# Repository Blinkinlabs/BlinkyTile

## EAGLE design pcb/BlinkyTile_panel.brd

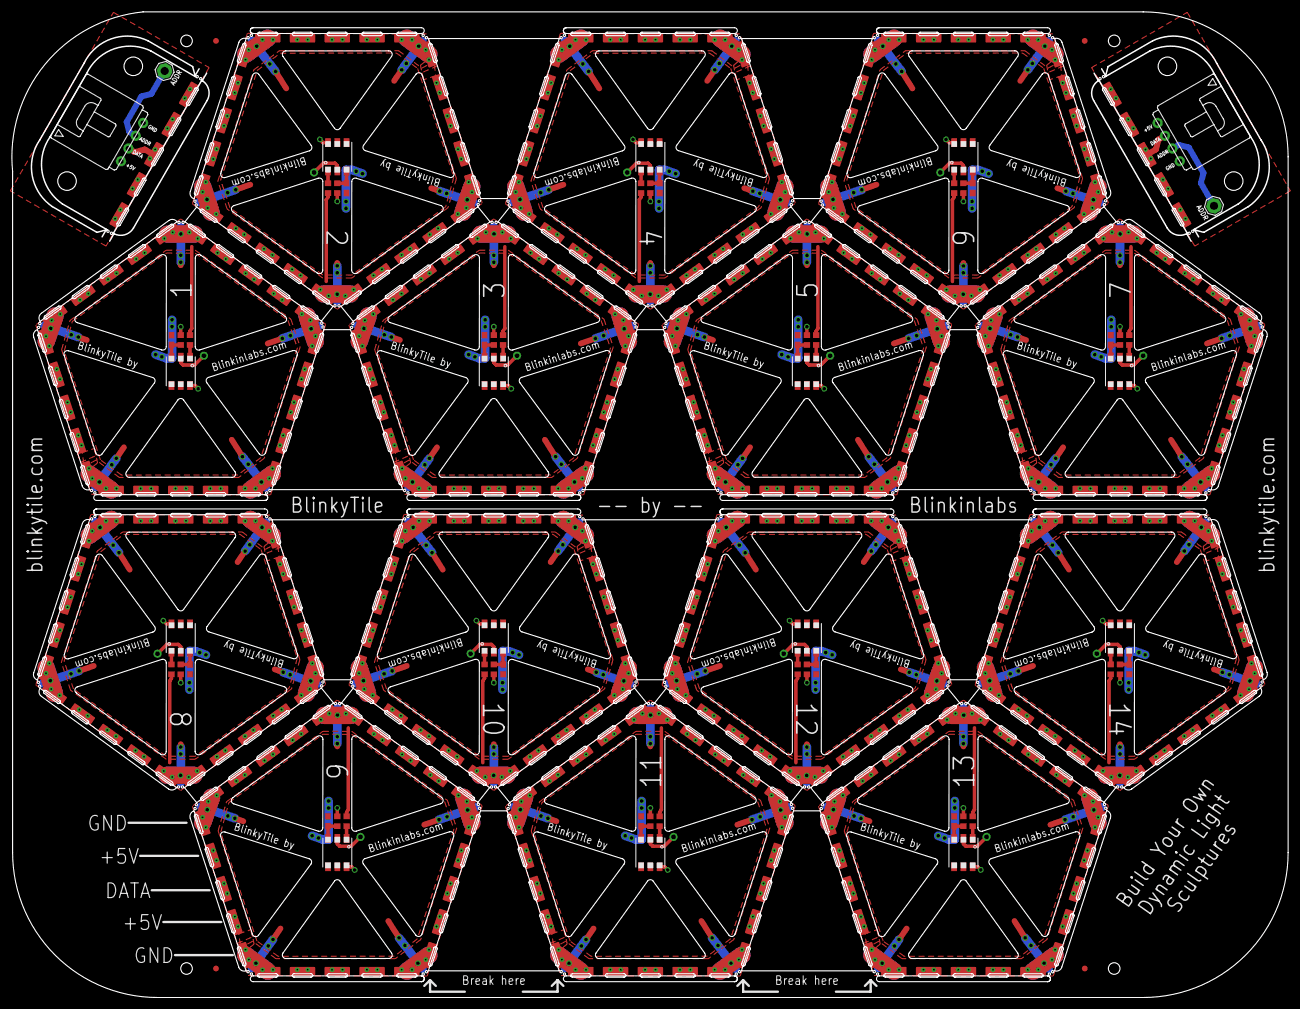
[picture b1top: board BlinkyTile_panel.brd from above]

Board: 2 copper layers, 220.1 x 170.0 mm, 210 parts (0 on the bottom side), 78 nets.

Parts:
C1, C2, C3, C5, C6, C7, C8, C9, C10, C11, C12, C13, C14, C15: .1uF; C0603
E$1, E$2, E$3, E$4, E$5, E$6, E$7, E$8, E$9, E$10, E$11, E$12, E$13, E$14, E$15, E$21, E$22, E$23, E$24, E$25, E$26, E$27, E$28, E$29, E$30, E$31, E$32, E$33, E$34, E$35, E$36, E$37, E$38, E$39, E$40, E$41, E$42, E$43, E$44, E$45, E$46, E$47, E$48, E$49, E$50, E$51, E$52, E$53, E$54, E$55, E$56, E$57, E$58, E$59, E$60, E$61, E$62, E$63, E$64, E$65, E$66, E$67, E$68, E$69, E$70, E$71, E$72, E$73, E$74, E$75: MOUSE_BITE_1
E$16, E$17, E$19, E$20: MOUSE_BITE
E$18, E$76: DUPONT-4P
E$77, E$78, E$79, E$80: FIDUCIAL-1X2
PROG, PROG1: SE14
R1, R3, R5, R9, R11, R13, R15, R17, R19, R21, R23, R25, R27, R29: 75; R0603
R2, R4, R6, R10, R12, R14, R16, R18, R20, R22, R24, R26, R28, R30: 10k; R0603
U$1, U$2, U$3, U$4, U$5, U$6, U$8, U$9, U$10, U$11, U$13, U$14, U$15, U$16, U$17, U$19, U$25, U$26, U$27, U$28, U$29, U$31, U$32, U$33, U$34, U$35, U$37, U$38, U$39, U$40, U$41, U$43, U$44, U$45, U$46, U$47, U$49, U$50, U$51, U$52, U$53, U$55, U$56, U$57, U$58, U$59, U$61, U$62, U$63, U$64, U$65, U$67, U$68, U$69, U$70, U$71, U$73, U$74, U$75, U$76, U$77, U$79, U$80, U$81, U$82, U$83, U$85, U$86, U$87, U$88, U$89, U$91: D_EDGEMOD; D_EDGE_SLOT_MOD
U$7, U$12, U$18, U$30, U$36, U$42, U$48, U$54, U$60, U$66, U$72, U$78, U$84, U$90: WS2822S_LED

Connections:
5V: R1.1, U$2.P$2, U$2.P$4, U$2.P$7, U$2.P$9, U$2.PWRVIA1, U$2.PWRVIA3, U$2.PWRVIA4, U$2.PWRVIA6, U$3.P$2, U$3.P$4, U$3.P$7, U$3.P$9, U$3.PWRVIA1, U$3.PWRVIA3, U$3.PWRVIA4, U$3.PWRVIA6, U$4.P$2, U$4.P$4, U$4.P$7, U$4.P$9, U$4.PWRVIA1, U$4.PWRVIA3, U$4.PWRVIA4, U$4.PWRVIA6, U$5.P$2, U$5.P$4, U$5.P$7, U$5.P$9, U$5.PWRVIA1, U$5.PWRVIA3, U$5.PWRVIA4, U$5.PWRVIA6, U$6.P$2, U$6.P$4, U$6.P$7, U$6.P$9, U$6.PWRVIA1, U$6.PWRVIA3, U$6.PWRVIA4, U$6.PWRVIA6, U$7.6
5V1: R3.1, U$1.P$2, U$1.P$4, U$1.P$7, U$1.P$9, U$1.PWRVIA1, U$1.PWRVIA3, U$1.PWRVIA4, U$1.PWRVIA6, U$8.P$2, U$8.P$4, U$8.P$7, U$8.P$9, U$8.PWRVIA1, U$8.PWRVIA3, U$8.PWRVIA4, U$8.PWRVIA6, U$9.P$2, U$9.P$4, U$9.P$7, U$9.P$9, U$9.PWRVIA1, U$9.PWRVIA3, U$9.PWRVIA4, U$9.PWRVIA6, U$10.P$2, U$10.P$4, U$10.P$7, U$10.P$9, U$10.PWRVIA1, U$10.PWRVIA3, U$10.PWRVIA4, U$10.PWRVIA6, U$11.P$2, U$11.P$4, U$11.P$7, U$11.P$9, U$11.PWRVIA1, U$11.PWRVIA3, U$11.PWRVIA4, U$11.PWRVIA6, U$12.6
5V2: R5.1, U$13.P$2, U$13.P$4, U$13.P$7, U$13.P$9, U$13.PWRVIA1, U$13.PWRVIA3, U$13.PWRVIA4, U$13.PWRVIA6, U$14.P$2, U$14.P$4, U$14.P$7, U$14.P$9, U$14.PWRVIA1, U$14.PWRVIA3, U$14.PWRVIA4, U$14.PWRVIA6, U$15.P$2, U$15.P$4, U$15.P$7, U$15.P$9, U$15.PWRVIA1, U$15.PWRVIA3, U$15.PWRVIA4, U$15.PWRVIA6, U$16.P$2, U$16.P$4, U$16.P$7, U$16.P$9, U$16.PWRVIA1, U$16.PWRVIA3, U$16.PWRVIA4, U$16.PWRVIA6, U$17.P$2, U$17.P$4, U$17.P$7, U$17.P$9, U$17.PWRVIA1, U$17.PWRVIA3, U$17.PWRVIA4, U$17.PWRVIA6, U$18.6
5V4: R9.1, U$25.P$2, U$25.P$4, U$25.P$7, U$25.P$9, U$25.PWRVIA1, U$25.PWRVIA3, U$25.PWRVIA4, U$25.PWRVIA6, U$26.P$2, U$26.P$4, U$26.P$7, U$26.P$9, U$26.PWRVIA1, U$26.PWRVIA3, U$26.PWRVIA4, U$26.PWRVIA6, U$27.P$2, U$27.P$4, U$27.P$7, U$27.P$9, U$27.PWRVIA1, U$27.PWRVIA3, U$27.PWRVIA4, U$27.PWRVIA6, U$28.P$2, U$28.P$4, U$28.P$7, U$28.P$9, U$28.PWRVIA1, U$28.PWRVIA3, U$28.PWRVIA4, U$28.PWRVIA6, U$29.P$2, U$29.P$4, U$29.P$7, U$29.P$9, U$29.PWRVIA1, U$29.PWRVIA3, U$29.PWRVIA4, U$29.PWRVIA6, U$30.6
5V5: R11.1, U$31.P$2, U$31.P$4, U$31.P$7, U$31.P$9, U$31.PWRVIA1, U$31.PWRVIA3, U$31.PWRVIA4, U$31.PWRVIA6, U$32.P$2, U$32.P$4, U$32.P$7, U$32.P$9, U$32.PWRVIA1, U$32.PWRVIA3, U$32.PWRVIA4, U$32.PWRVIA6, U$33.P$2, U$33.P$4, U$33.P$7, U$33.P$9, U$33.PWRVIA1, U$33.PWRVIA3, U$33.PWRVIA4, U$33.PWRVIA6, U$34.P$2, U$34.P$4, U$34.P$7, U$34.P$9, U$34.PWRVIA1, U$34.PWRVIA3, U$34.PWRVIA4, U$34.PWRVIA6, U$35.P$2, U$35.P$4, U$35.P$7, U$35.P$9, U$35.PWRVIA1, U$35.PWRVIA3, U$35.PWRVIA4, U$35.PWRVIA6, U$36.6
5V6: R13.1, U$37.P$2, U$37.P$4, U$37.P$7, U$37.P$9, U$37.PWRVIA1, U$37.PWRVIA3, U$37.PWRVIA4, U$37.PWRVIA6, U$38.P$2, U$38.P$4, U$38.P$7, U$38.P$9, U$38.PWRVIA1, U$38.PWRVIA3, U$38.PWRVIA4, U$38.PWRVIA6, U$39.P$2, U$39.P$4, U$39.P$7, U$39.P$9, U$39.PWRVIA1, U$39.PWRVIA3, U$39.PWRVIA4, U$39.PWRVIA6, U$40.P$2, U$40.P$4, U$40.P$7, U$40.P$9, U$40.PWRVIA1, U$40.PWRVIA3, U$40.PWRVIA4, U$40.PWRVIA6, U$41.P$2, U$41.P$4, U$41.P$7, U$41.P$9, U$41.PWRVIA1, U$41.PWRVIA3, U$41.PWRVIA4, U$41.PWRVIA6, U$42.6
5V7: R15.1, U$43.P$2, U$43.P$4, U$43.P$7, U$43.P$9, U$43.PWRVIA1, U$43.PWRVIA3, U$43.PWRVIA4, U$43.PWRVIA6, U$44.P$2, U$44.P$4, U$44.P$7, U$44.P$9, U$44.PWRVIA1, U$44.PWRVIA3, U$44.PWRVIA4, U$44.PWRVIA6, U$45.P$2, U$45.P$4, U$45.P$7, U$45.P$9, U$45.PWRVIA1, U$45.PWRVIA3, U$45.PWRVIA4, U$45.PWRVIA6, U$46.P$2, U$46.P$4, U$46.P$7, U$46.P$9, U$46.PWRVIA1, U$46.PWRVIA3, U$46.PWRVIA4, U$46.PWRVIA6, U$47.P$2, U$47.P$4, U$47.P$7, U$47.P$9, U$47.PWRVIA1, U$47.PWRVIA3, U$47.PWRVIA4, U$47.PWRVIA6, U$48.6
5V8: R17.1, U$49.P$2, U$49.P$4, U$49.P$7, U$49.P$9, U$49.PWRVIA1, U$49.PWRVIA3, U$49.PWRVIA4, U$49.PWRVIA6, U$50.P$2, U$50.P$4, U$50.P$7, U$50.P$9, U$50.PWRVIA1, U$50.PWRVIA3, U$50.PWRVIA4, U$50.PWRVIA6, U$51.P$2, U$51.P$4, U$51.P$7, U$51.P$9, U$51.PWRVIA1, U$51.PWRVIA3, U$51.PWRVIA4, U$51.PWRVIA6, U$52.P$2, U$52.P$4, U$52.P$7, U$52.P$9, U$52.PWRVIA1, U$52.PWRVIA3, U$52.PWRVIA4, U$52.PWRVIA6, U$53.P$2, U$53.P$4, U$53.P$7, U$53.P$9, U$53.PWRVIA1, U$53.PWRVIA3, U$53.PWRVIA4, U$53.PWRVIA6, U$54.6
5V9: R19.1, U$55.P$2, U$55.P$4, U$55.P$7, U$55.P$9, U$55.PWRVIA1, U$55.PWRVIA3, U$55.PWRVIA4, U$55.PWRVIA6, U$56.P$2, U$56.P$4, U$56.P$7, U$56.P$9, U$56.PWRVIA1, U$56.PWRVIA3, U$56.PWRVIA4, U$56.PWRVIA6, U$57.P$2, U$57.P$4, U$57.P$7, U$57.P$9, U$57.PWRVIA1, U$57.PWRVIA3, U$57.PWRVIA4, U$57.PWRVIA6, U$58.P$2, U$58.P$4, U$58.P$7, U$58.P$9, U$58.PWRVIA1, U$58.PWRVIA3, U$58.PWRVIA4, U$58.PWRVIA6, U$59.P$2, U$59.P$4, U$59.P$7, U$59.P$9, U$59.PWRVIA1, U$59.PWRVIA3, U$59.PWRVIA4, U$59.PWRVIA6, U$60.6
5V10: R21.1, U$61.P$2, U$61.P$4, U$61.P$7, U$61.P$9, U$61.PWRVIA1, U$61.PWRVIA3, U$61.PWRVIA4, U$61.PWRVIA6, U$62.P$2, U$62.P$4, U$62.P$7, U$62.P$9, U$62.PWRVIA1, U$62.PWRVIA3, U$62.PWRVIA4, U$62.PWRVIA6, U$63.P$2, U$63.P$4, U$63.P$7, U$63.P$9, U$63.PWRVIA1, U$63.PWRVIA3, U$63.PWRVIA4, U$63.PWRVIA6, U$64.P$2, U$64.P$4, U$64.P$7, U$64.P$9, U$64.PWRVIA1, U$64.PWRVIA3, U$64.PWRVIA4, U$64.PWRVIA6, U$65.P$2, U$65.P$4, U$65.P$7, U$65.P$9, U$65.PWRVIA1, U$65.PWRVIA3, U$65.PWRVIA4, U$65.PWRVIA6, U$66.6
5V11: R23.1, U$67.P$2, U$67.P$4, U$67.P$7, U$67.P$9, U$67.PWRVIA1, U$67.PWRVIA3, U$67.PWRVIA4, U$67.PWRVIA6, U$68.P$2, U$68.P$4, U$68.P$7, U$68.P$9, U$68.PWRVIA1, U$68.PWRVIA3, U$68.PWRVIA4, U$68.PWRVIA6, U$69.P$2, U$69.P$4, U$69.P$7, U$69.P$9, U$69.PWRVIA1, U$69.PWRVIA3, U$69.PWRVIA4, U$69.PWRVIA6, U$70.P$2, U$70.P$4, U$70.P$7, U$70.P$9, U$70.PWRVIA1, U$70.PWRVIA3, U$70.PWRVIA4, U$70.PWRVIA6, U$71.P$2, U$71.P$4, U$71.P$7, U$71.P$9, U$71.PWRVIA1, U$71.PWRVIA3, U$71.PWRVIA4, U$71.PWRVIA6, U$72.6
5V12: R25.1, U$73.P$2, U$73.P$4, U$73.P$7, U$73.P$9, U$73.PWRVIA1, U$73.PWRVIA3, U$73.PWRVIA4, U$73.PWRVIA6, U$74.P$2, U$74.P$4, U$74.P$7, U$74.P$9, U$74.PWRVIA1, U$74.PWRVIA3, U$74.PWRVIA4, U$74.PWRVIA6, U$75.P$2, U$75.P$4, U$75.P$7, U$75.P$9, U$75.PWRVIA1, U$75.PWRVIA3, U$75.PWRVIA4, U$75.PWRVIA6, U$76.P$2, U$76.P$4, U$76.P$7, U$76.P$9, U$76.PWRVIA1, U$76.PWRVIA3, U$76.PWRVIA4, U$76.PWRVIA6, U$77.P$2, U$77.P$4, U$77.P$7, U$77.P$9, U$77.PWRVIA1, U$77.PWRVIA3, U$77.PWRVIA4, U$77.PWRVIA6, U$78.6
5V13: R27.1, U$79.P$2, U$79.P$4, U$79.P$7, U$79.P$9, U$79.PWRVIA1, U$79.PWRVIA3, U$79.PWRVIA4, U$79.PWRVIA6, U$80.P$2, U$80.P$4, U$80.P$7, U$80.P$9, U$80.PWRVIA1, U$80.PWRVIA3, U$80.PWRVIA4, U$80.PWRVIA6, U$81.P$2, U$81.P$4, U$81.P$7, U$81.P$9, U$81.PWRVIA1, U$81.PWRVIA3, U$81.PWRVIA4, U$81.PWRVIA6, U$82.P$2, U$82.P$4, U$82.P$7, U$82.P$9, U$82.PWRVIA1, U$82.PWRVIA3, U$82.PWRVIA4, U$82.PWRVIA6, U$83.P$2, U$83.P$4, U$83.P$7, U$83.P$9, U$83.PWRVIA1, U$83.PWRVIA3, U$83.PWRVIA4, U$83.PWRVIA6, U$84.6
5V14: R29.1, U$85.P$2, U$85.P$4, U$85.P$7, U$85.P$9, U$85.PWRVIA1, U$85.PWRVIA3, U$85.PWRVIA4, U$85.PWRVIA6, U$86.P$2, U$86.P$4, U$86.P$7, U$86.P$9, U$86.PWRVIA1, U$86.PWRVIA3, U$86.PWRVIA4, U$86.PWRVIA6, U$87.P$2, U$87.P$4, U$87.P$7, U$87.P$9, U$87.PWRVIA1, U$87.PWRVIA3, U$87.PWRVIA4, U$87.PWRVIA6, U$88.P$2, U$88.P$4, U$88.P$7, U$88.P$9, U$88.PWRVIA1, U$88.PWRVIA3, U$88.PWRVIA4, U$88.PWRVIA6, U$89.P$2, U$89.P$4, U$89.P$7, U$89.P$9, U$89.PWRVIA1, U$89.PWRVIA3, U$89.PWRVIA4, U$89.PWRVIA6, U$90.6
DATA: R2.2, U$2.P$3, U$2.P$8, U$2.SIGVIA1, U$2.SIGVIA3, U$3.P$3, U$3.P$8, U$3.SIGVIA1, U$3.SIGVIA3, U$4.P$3, U$4.P$8, U$4.SIGVIA1, U$4.SIGVIA3, U$5.P$3, U$5.P$8, U$5.SIGVIA1, U$5.SIGVIA3, U$6.P$3, U$6.P$8, U$6.SIGVIA1, U$6.SIGVIA3
DATA1: R4.2, U$1.P$3, U$1.P$8, U$1.SIGVIA1, U$1.SIGVIA3, U$8.P$3, U$8.P$8, U$8.SIGVIA1, U$8.SIGVIA3, U$9.P$3, U$9.P$8, U$9.SIGVIA1, U$9.SIGVIA3, U$10.P$3, U$10.P$8, U$10.SIGVIA1, U$10.SIGVIA3, U$11.P$3, U$11.P$8, U$11.SIGVIA1, U$11.SIGVIA3
DATA2: R6.2, U$13.P$3, U$13.P$8, U$13.SIGVIA1, U$13.SIGVIA3, U$14.P$3, U$14.P$8, U$14.SIGVIA1, U$14.SIGVIA3, U$15.P$3, U$15.P$8, U$15.SIGVIA1, U$15.SIGVIA3, U$16.P$3, U$16.P$8, U$16.SIGVIA1, U$16.SIGVIA3, U$17.P$3, U$17.P$8, U$17.SIGVIA1, U$17.SIGVIA3
DATA4: R10.2, U$25.P$3, U$25.P$8, U$25.SIGVIA1, U$25.SIGVIA3, U$26.P$3, U$26.P$8, U$26.SIGVIA1, U$26.SIGVIA3, U$27.P$3, U$27.P$8, U$27.SIGVIA1, U$27.SIGVIA3, U$28.P$3, U$28.P$8, U$28.SIGVIA1, U$28.SIGVIA3, U$29.P$3, U$29.P$8, U$29.SIGVIA1, U$29.SIGVIA3
DATA5: R12.2, U$31.P$3, U$31.P$8, U$31.SIGVIA1, U$31.SIGVIA3, U$32.P$3, U$32.P$8, U$32.SIGVIA1, U$32.SIGVIA3, U$33.P$3, U$33.P$8, U$33.SIGVIA1, U$33.SIGVIA3, U$34.P$3, U$34.P$8, U$34.SIGVIA1, U$34.SIGVIA3, U$35.P$3, U$35.P$8, U$35.SIGVIA1, U$35.SIGVIA3
DATA6: R14.2, U$37.P$3, U$37.P$8, U$37.SIGVIA1, U$37.SIGVIA3, U$38.P$3, U$38.P$8, U$38.SIGVIA1, U$38.SIGVIA3, U$39.P$3, U$39.P$8, U$39.SIGVIA1, U$39.SIGVIA3, U$40.P$3, U$40.P$8, U$40.SIGVIA1, U$40.SIGVIA3, U$41.P$3, U$41.P$8, U$41.SIGVIA1, U$41.SIGVIA3
DATA7: R16.2, U$43.P$3, U$43.P$8, U$43.SIGVIA1, U$43.SIGVIA3, U$44.P$3, U$44.P$8, U$44.SIGVIA1, U$44.SIGVIA3, U$45.P$3, U$45.P$8, U$45.SIGVIA1, U$45.SIGVIA3, U$46.P$3, U$46.P$8, U$46.SIGVIA1, U$46.SIGVIA3, U$47.P$3, U$47.P$8, U$47.SIGVIA1, U$47.SIGVIA3
DATA8: R18.2, U$49.P$3, U$49.P$8, U$49.SIGVIA1, U$49.SIGVIA3, U$50.P$3, U$50.P$8, U$50.SIGVIA1, U$50.SIGVIA3, U$51.P$3, U$51.P$8, U$51.SIGVIA1, U$51.SIGVIA3, U$52.P$3, U$52.P$8, U$52.SIGVIA1, U$52.SIGVIA3, U$53.P$3, U$53.P$8, U$53.SIGVIA1, U$53.SIGVIA3
DATA9: R20.2, U$55.P$3, U$55.P$8, U$55.SIGVIA1, U$55.SIGVIA3, U$56.P$3, U$56.P$8, U$56.SIGVIA1, U$56.SIGVIA3, U$57.P$3, U$57.P$8, U$57.SIGVIA1, U$57.SIGVIA3, U$58.P$3, U$58.P$8, U$58.SIGVIA1, U$58.SIGVIA3, U$59.P$3, U$59.P$8, U$59.SIGVIA1, U$59.SIGVIA3
DATA10: R22.2, U$61.P$3, U$61.P$8, U$61.SIGVIA1, U$61.SIGVIA3, U$62.P$3, U$62.P$8, U$62.SIGVIA1, U$62.SIGVIA3, U$63.P$3, U$63.P$8, U$63.SIGVIA1, U$63.SIGVIA3, U$64.P$3, U$64.P$8, U$64.SIGVIA1, U$64.SIGVIA3, U$65.P$3, U$65.P$8, U$65.SIGVIA1, U$65.SIGVIA3
DATA11: R24.2, U$67.P$3, U$67.P$8, U$67.SIGVIA1, U$67.SIGVIA3, U$68.P$3, U$68.P$8, U$68.SIGVIA1, U$68.SIGVIA3, U$69.P$3, U$69.P$8, U$69.SIGVIA1, U$69.SIGVIA3, U$70.P$3, U$70.P$8, U$70.SIGVIA1, U$70.SIGVIA3, U$71.P$3, U$71.P$8, U$71.SIGVIA1, U$71.SIGVIA3
DATA12: R26.2, U$73.P$3, U$73.P$8, U$73.SIGVIA1, U$73.SIGVIA3, U$74.P$3, U$74.P$8, U$74.SIGVIA1, U$74.SIGVIA3, U$75.P$3, U$75.P$8, U$75.SIGVIA1, U$75.SIGVIA3, U$76.P$3, U$76.P$8, U$76.SIGVIA1, U$76.SIGVIA3, U$77.P$3, U$77.P$8, U$77.SIGVIA1, U$77.SIGVIA3
DATA13: R28.2, U$79.P$3, U$79.P$8, U$79.SIGVIA1, U$79.SIGVIA3, U$80.P$3, U$80.P$8, U$80.SIGVIA1, U$80.SIGVIA3, U$81.P$3, U$81.P$8, U$81.SIGVIA1, U$81.SIGVIA3, U$82.P$3, U$82.P$8, U$82.SIGVIA1, U$82.SIGVIA3, U$83.P$3, U$83.P$8, U$83.SIGVIA1, U$83.SIGVIA3
DATA14: R30.2, U$85.P$3, U$85.P$8, U$85.SIGVIA1, U$85.SIGVIA3, U$86.P$3, U$86.P$8, U$86.SIGVIA1, U$86.SIGVIA3, U$87.P$3, U$87.P$8, U$87.SIGVIA1, U$87.SIGVIA3, U$88.P$3, U$88.P$8, U$88.SIGVIA1, U$88.SIGVIA3, U$89.P$3, U$89.P$8, U$89.SIGVIA1, U$89.SIGVIA3
GND: C1.2, U$2.GNDVIA1, U$2.GNDVIA3, U$2.GNDVIA4, U$2.GNDVIA6, U$2.P$1, U$2.P$5, U$2.P$6, U$2.P$10, U$3.GNDVIA1, U$3.GNDVIA3, U$3.GNDVIA4, U$3.GNDVIA6, U$3.P$1, U$3.P$5, U$3.P$6, U$3.P$10, U$4.GNDVIA1, U$4.GNDVIA3, U$4.GNDVIA4, U$4.GNDVIA6, U$4.P$1, U$4.P$5, U$4.P$6, U$4.P$10, U$5.GNDVIA1, U$5.GNDVIA3, U$5.GNDVIA4, U$5.GNDVIA6, U$5.P$1, U$5.P$5, U$5.P$6, U$5.P$10, U$6.GNDVIA1, U$6.GNDVIA3, U$6.GNDVIA4, U$6.GNDVIA6, U$6.P$1, U$6.P$5, U$6.P$6, U$6.P$10, U$7.4
GND1: C2.2, U$1.GNDVIA1, U$1.GNDVIA3, U$1.GNDVIA4, U$1.GNDVIA6, U$1.P$1, U$1.P$5, U$1.P$6, U$1.P$10, U$8.GNDVIA1, U$8.GNDVIA3, U$8.GNDVIA4, U$8.GNDVIA6, U$8.P$1, U$8.P$5, U$8.P$6, U$8.P$10, U$9.GNDVIA1, U$9.GNDVIA3, U$9.GNDVIA4, U$9.GNDVIA6, U$9.P$1, U$9.P$5, U$9.P$6, U$9.P$10, U$10.GNDVIA1, U$10.GNDVIA3, U$10.GNDVIA4, U$10.GNDVIA6, U$10.P$1, U$10.P$5, U$10.P$6, U$10.P$10, U$11.GNDVIA1, U$11.GNDVIA3, U$11.GNDVIA4, U$11.GNDVIA6, U$11.P$1, U$11.P$5, U$11.P$6, U$11.P$10, U$12.4
GND2: C3.2, U$13.GNDVIA1, U$13.GNDVIA3, U$13.GNDVIA4, U$13.GNDVIA6, U$13.P$1, U$13.P$5, U$13.P$6, U$13.P$10, U$14.GNDVIA1, U$14.GNDVIA3, U$14.GNDVIA4, U$14.GNDVIA6, U$14.P$1, U$14.P$5, U$14.P$6, U$14.P$10, U$15.GNDVIA1, U$15.GNDVIA3, U$15.GNDVIA4, U$15.GNDVIA6, U$15.P$1, U$15.P$5, U$15.P$6, U$15.P$10, U$16.GNDVIA1, U$16.GNDVIA3, U$16.GNDVIA4, U$16.GNDVIA6, U$16.P$1, U$16.P$5, U$16.P$6, U$16.P$10, U$17.GNDVIA1, U$17.GNDVIA3, U$17.GNDVIA4, U$17.GNDVIA6, U$17.P$1, U$17.P$5, U$17.P$6, U$17.P$10, U$18.4
GND4: C5.2, U$25.GNDVIA1, U$25.GNDVIA3, U$25.GNDVIA4, U$25.GNDVIA6, U$25.P$1, U$25.P$5, U$25.P$6, U$25.P$10, U$26.GNDVIA1, U$26.GNDVIA3, U$26.GNDVIA4, U$26.GNDVIA6, U$26.P$1, U$26.P$5, U$26.P$6, U$26.P$10, U$27.GNDVIA1, U$27.GNDVIA3, U$27.GNDVIA4, U$27.GNDVIA6, U$27.P$1, U$27.P$5, U$27.P$6, U$27.P$10, U$28.GNDVIA1, U$28.GNDVIA3, U$28.GNDVIA4, U$28.GNDVIA6, U$28.P$1, U$28.P$5, U$28.P$6, U$28.P$10, U$29.GNDVIA1, U$29.GNDVIA3, U$29.GNDVIA4, U$29.GNDVIA6, U$29.P$1, U$29.P$5, U$29.P$6, U$29.P$10, U$30.4
GND5: C6.2, U$31.GNDVIA1, U$31.GNDVIA3, U$31.GNDVIA4, U$31.GNDVIA6, U$31.P$1, U$31.P$5, U$31.P$6, U$31.P$10, U$32.GNDVIA1, U$32.GNDVIA3, U$32.GNDVIA4, U$32.GNDVIA6, U$32.P$1, U$32.P$5, U$32.P$6, U$32.P$10, U$33.GNDVIA1, U$33.GNDVIA3, U$33.GNDVIA4, U$33.GNDVIA6, U$33.P$1, U$33.P$5, U$33.P$6, U$33.P$10, U$34.GNDVIA1, U$34.GNDVIA3, U$34.GNDVIA4, U$34.GNDVIA6, U$34.P$1, U$34.P$5, U$34.P$6, U$34.P$10, U$35.GNDVIA1, U$35.GNDVIA3, U$35.GNDVIA4, U$35.GNDVIA6, U$35.P$1, U$35.P$5, U$35.P$6, U$35.P$10, U$36.4
GND6: C7.2, U$37.GNDVIA1, U$37.GNDVIA3, U$37.GNDVIA4, U$37.GNDVIA6, U$37.P$1, U$37.P$5, U$37.P$6, U$37.P$10, U$38.GNDVIA1, U$38.GNDVIA3, U$38.GNDVIA4, U$38.GNDVIA6, U$38.P$1, U$38.P$5, U$38.P$6, U$38.P$10, U$39.GNDVIA1, U$39.GNDVIA3, U$39.GNDVIA4, U$39.GNDVIA6, U$39.P$1, U$39.P$5, U$39.P$6, U$39.P$10, U$40.GNDVIA1, U$40.GNDVIA3, U$40.GNDVIA4, U$40.GNDVIA6, U$40.P$1, U$40.P$5, U$40.P$6, U$40.P$10, U$41.GNDVIA1, U$41.GNDVIA3, U$41.GNDVIA4, U$41.GNDVIA6, U$41.P$1, U$41.P$5, U$41.P$6, U$41.P$10, U$42.4
GND7: C8.2, U$43.GNDVIA1, U$43.GNDVIA3, U$43.GNDVIA4, U$43.GNDVIA6, U$43.P$1, U$43.P$5, U$43.P$6, U$43.P$10, U$44.GNDVIA1, U$44.GNDVIA3, U$44.GNDVIA4, U$44.GNDVIA6, U$44.P$1, U$44.P$5, U$44.P$6, U$44.P$10, U$45.GNDVIA1, U$45.GNDVIA3, U$45.GNDVIA4, U$45.GNDVIA6, U$45.P$1, U$45.P$5, U$45.P$6, U$45.P$10, U$46.GNDVIA1, U$46.GNDVIA3, U$46.GNDVIA4, U$46.GNDVIA6, U$46.P$1, U$46.P$5, U$46.P$6, U$46.P$10, U$47.GNDVIA1, U$47.GNDVIA3, U$47.GNDVIA4, U$47.GNDVIA6, U$47.P$1, U$47.P$5, U$47.P$6, U$47.P$10, U$48.4
GND8: C9.2, U$49.GNDVIA1, U$49.GNDVIA3, U$49.GNDVIA4, U$49.GNDVIA6, U$49.P$1, U$49.P$5, U$49.P$6, U$49.P$10, U$50.GNDVIA1, U$50.GNDVIA3, U$50.GNDVIA4, U$50.GNDVIA6, U$50.P$1, U$50.P$5, U$50.P$6, U$50.P$10, U$51.GNDVIA1, U$51.GNDVIA3, U$51.GNDVIA4, U$51.GNDVIA6, U$51.P$1, U$51.P$5, U$51.P$6, U$51.P$10, U$52.GNDVIA1, U$52.GNDVIA3, U$52.GNDVIA4, U$52.GNDVIA6, U$52.P$1, U$52.P$5, U$52.P$6, U$52.P$10, U$53.GNDVIA1, U$53.GNDVIA3, U$53.GNDVIA4, U$53.GNDVIA6, U$53.P$1, U$53.P$5, U$53.P$6, U$53.P$10, U$54.4
GND9: C10.2, U$55.GNDVIA1, U$55.GNDVIA3, U$55.GNDVIA4, U$55.GNDVIA6, U$55.P$1, U$55.P$5, U$55.P$6, U$55.P$10, U$56.GNDVIA1, U$56.GNDVIA3, U$56.GNDVIA4, U$56.GNDVIA6, U$56.P$1, U$56.P$5, U$56.P$6, U$56.P$10, U$57.GNDVIA1, U$57.GNDVIA3, U$57.GNDVIA4, U$57.GNDVIA6, U$57.P$1, U$57.P$5, U$57.P$6, U$57.P$10, U$58.GNDVIA1, U$58.GNDVIA3, U$58.GNDVIA4, U$58.GNDVIA6, U$58.P$1, U$58.P$5, U$58.P$6, U$58.P$10, U$59.GNDVIA1, U$59.GNDVIA3, U$59.GNDVIA4, U$59.GNDVIA6, U$59.P$1, U$59.P$5, U$59.P$6, U$59.P$10, U$60.4
GND10: C11.2, U$61.GNDVIA1, U$61.GNDVIA3, U$61.GNDVIA4, U$61.GNDVIA6, U$61.P$1, U$61.P$5, U$61.P$6, U$61.P$10, U$62.GNDVIA1, U$62.GNDVIA3, U$62.GNDVIA4, U$62.GNDVIA6, U$62.P$1, U$62.P$5, U$62.P$6, U$62.P$10, U$63.GNDVIA1, U$63.GNDVIA3, U$63.GNDVIA4, U$63.GNDVIA6, U$63.P$1, U$63.P$5, U$63.P$6, U$63.P$10, U$64.GNDVIA1, U$64.GNDVIA3, U$64.GNDVIA4, U$64.GNDVIA6, U$64.P$1, U$64.P$5, U$64.P$6, U$64.P$10, U$65.GNDVIA1, U$65.GNDVIA3, U$65.GNDVIA4, U$65.GNDVIA6, U$65.P$1, U$65.P$5, U$65.P$6, U$65.P$10, U$66.4
GND11: C12.2, U$67.GNDVIA1, U$67.GNDVIA3, U$67.GNDVIA4, U$67.GNDVIA6, U$67.P$1, U$67.P$5, U$67.P$6, U$67.P$10, U$68.GNDVIA1, U$68.GNDVIA3, U$68.GNDVIA4, U$68.GNDVIA6, U$68.P$1, U$68.P$5, U$68.P$6, U$68.P$10, U$69.GNDVIA1, U$69.GNDVIA3, U$69.GNDVIA4, U$69.GNDVIA6, U$69.P$1, U$69.P$5, U$69.P$6, U$69.P$10, U$70.GNDVIA1, U$70.GNDVIA3, U$70.GNDVIA4, U$70.GNDVIA6, U$70.P$1, U$70.P$5, U$70.P$6, U$70.P$10, U$71.GNDVIA1, U$71.GNDVIA3, U$71.GNDVIA4, U$71.GNDVIA6, U$71.P$1, U$71.P$5, U$71.P$6, U$71.P$10, U$72.4
GND12: C13.2, U$73.GNDVIA1, U$73.GNDVIA3, U$73.GNDVIA4, U$73.GNDVIA6, U$73.P$1, U$73.P$5, U$73.P$6, U$73.P$10, U$74.GNDVIA1, U$74.GNDVIA3, U$74.GNDVIA4, U$74.GNDVIA6, U$74.P$1, U$74.P$5, U$74.P$6, U$74.P$10, U$75.GNDVIA1, U$75.GNDVIA3, U$75.GNDVIA4, U$75.GNDVIA6, U$75.P$1, U$75.P$5, U$75.P$6, U$75.P$10, U$76.GNDVIA1, U$76.GNDVIA3, U$76.GNDVIA4, U$76.GNDVIA6, U$76.P$1, U$76.P$5, U$76.P$6, U$76.P$10, U$77.GNDVIA1, U$77.GNDVIA3, U$77.GNDVIA4, U$77.GNDVIA6, U$77.P$1, U$77.P$5, U$77.P$6, U$77.P$10, U$78.4
GND13: C14.2, U$79.GNDVIA1, U$79.GNDVIA3, U$79.GNDVIA4, U$79.GNDVIA6, U$79.P$1, U$79.P$5, U$79.P$6, U$79.P$10, U$80.GNDVIA1, U$80.GNDVIA3, U$80.GNDVIA4, U$80.GNDVIA6, U$80.P$1, U$80.P$5, U$80.P$6, U$80.P$10, U$81.GNDVIA1, U$81.GNDVIA3, U$81.GNDVIA4, U$81.GNDVIA6, U$81.P$1, U$81.P$5, U$81.P$6, U$81.P$10, U$82.GNDVIA1, U$82.GNDVIA3, U$82.GNDVIA4, U$82.GNDVIA6, U$82.P$1, U$82.P$5, U$82.P$6, U$82.P$10, U$83.GNDVIA1, U$83.GNDVIA3, U$83.GNDVIA4, U$83.GNDVIA6, U$83.P$1, U$83.P$5, U$83.P$6, U$83.P$10, U$84.4
GND14: C15.2, U$85.GNDVIA1, U$85.GNDVIA3, U$85.GNDVIA4, U$85.GNDVIA6, U$85.P$1, U$85.P$5, U$85.P$6, U$85.P$10, U$86.GNDVIA1, U$86.GNDVIA3, U$86.GNDVIA4, U$86.GNDVIA6, U$86.P$1, U$86.P$5, U$86.P$6, U$86.P$10, U$87.GNDVIA1, U$87.GNDVIA3, U$87.GNDVIA4, U$87.GNDVIA6, U$87.P$1, U$87.P$5, U$87.P$6, U$87.P$10, U$88.GNDVIA1, U$88.GNDVIA3, U$88.GNDVIA4, U$88.GNDVIA6, U$88.P$1, U$88.P$5, U$88.P$6, U$88.P$10, U$89.GNDVIA1, U$89.GNDVIA3, U$89.GNDVIA4, U$89.GNDVIA6, U$89.P$1, U$89.P$5, U$89.P$6, U$89.P$10, U$90.4
unnamed: C1.1, R1.2, U$7.3
unnamed: R2.1, U$7.1
unnamed: C2.1, R3.2, U$12.3
unnamed: R4.1, U$12.1
unnamed: C3.1, R5.2, U$18.3
unnamed: R6.1, U$18.1
unnamed: C5.1, R9.2, U$30.3
unnamed: R10.1, U$30.1
unnamed: C6.1, R11.2, U$36.3
unnamed: R12.1, U$36.1
unnamed: C7.1, R13.2, U$42.3
unnamed: R14.1, U$42.1
unnamed: C8.1, R15.2, U$48.3
unnamed: R16.1, U$48.1
unnamed: C9.1, R17.2, U$54.3
unnamed: R18.1, U$54.1
unnamed: C10.1, R19.2, U$60.3
unnamed: R20.1, U$60.1
unnamed: C11.1, R21.2, U$66.3
unnamed: R22.1, U$66.1
unnamed: C12.1, R23.2, U$72.3
unnamed: R24.1, U$72.1
unnamed: C13.1, R25.2, U$78.3
unnamed: R26.1, U$78.1
unnamed: C14.1, R27.2, U$84.3
unnamed: R28.1, U$84.1
unnamed: C15.1, R29.2, U$90.3
unnamed: R30.1, U$90.1
S$1: E$18.P$2, U$91.P$3
S$2: E$18.P$4, U$91.P$1, U$91.P$5
S$3: E$76.P$4, U$19.P$1, U$19.P$5
S$4: E$76.P$2, U$19.P$3
S$5: E$76.P$3, PROG1.MP
S$10: E$18.P$3, PROG.MP
VCC: E$18.P$1, U$91.P$7, U$91.P$9
VCC1: E$76.P$1, U$19.P$7, U$19.P$9

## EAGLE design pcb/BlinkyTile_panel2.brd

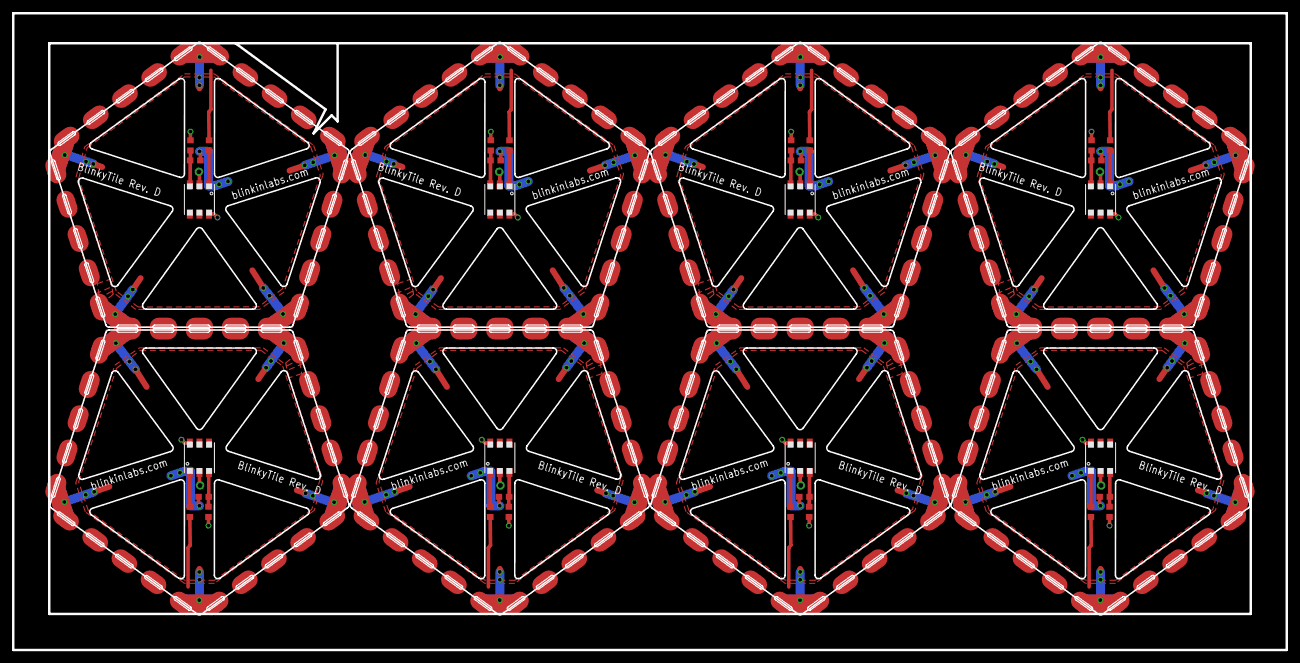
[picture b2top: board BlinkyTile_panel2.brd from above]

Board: 2 copper layers, 212.0 x 106.0 mm, 72 parts (0 on the bottom side), 40 nets.

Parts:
C1, C2, C3, C4, C5, C6, C7, C8: .1uF; C0603
R1, R3, R5, R7, R9, R11, R13, R15: 75; R0603
R2, R4, R6, R8, R10, R12, R14, R16: 10k; R0603
U$1, U$2, U$3, U$4, U$5, U$6, U$8, U$9, U$10, U$11, U$13, U$14, U$15, U$16, U$17, U$19, U$20, U$21, U$22, U$23, U$25, U$26, U$27, U$28, U$29, U$31, U$32, U$33, U$34, U$35, U$37, U$38, U$39, U$40, U$41, U$43, U$44, U$45, U$46, U$47: D_EDGESLOT; D_EDGE_SLOT
U$7, U$12, U$18, U$24, U$30, U$36, U$42, U$48: WS2822S_LED

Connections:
5V: R1.1, U$2.P$2, U$2.P$4, U$2.P$7, U$2.P$9, U$3.P$2, U$3.P$4, U$3.P$7, U$3.P$9, U$4.P$2, U$4.P$4, U$4.P$7, U$4.P$9, U$5.P$2, U$5.P$4, U$5.P$7, U$5.P$9, U$6.P$2, U$6.P$4, U$6.P$7, U$6.P$9, U$7.6
5V1: R3.1, U$1.P$2, U$1.P$4, U$1.P$7, U$1.P$9, U$8.P$2, U$8.P$4, U$8.P$7, U$8.P$9, U$9.P$2, U$9.P$4, U$9.P$7, U$9.P$9, U$10.P$2, U$10.P$4, U$10.P$7, U$10.P$9, U$11.P$2, U$11.P$4, U$11.P$7, U$11.P$9, U$12.6
5V2: R5.1, U$13.P$2, U$13.P$4, U$13.P$7, U$13.P$9, U$14.P$2, U$14.P$4, U$14.P$7, U$14.P$9, U$15.P$2, U$15.P$4, U$15.P$7, U$15.P$9, U$16.P$2, U$16.P$4, U$16.P$7, U$16.P$9, U$17.P$2, U$17.P$4, U$17.P$7, U$17.P$9, U$18.6
5V3: R7.1, U$19.P$2, U$19.P$4, U$19.P$7, U$19.P$9, U$20.P$2, U$20.P$4, U$20.P$7, U$20.P$9, U$21.P$2, U$21.P$4, U$21.P$7, U$21.P$9, U$22.P$2, U$22.P$4, U$22.P$7, U$22.P$9, U$23.P$2, U$23.P$4, U$23.P$7, U$23.P$9, U$24.6
5V4: R9.1, U$25.P$2, U$25.P$4, U$25.P$7, U$25.P$9, U$26.P$2, U$26.P$4, U$26.P$7, U$26.P$9, U$27.P$2, U$27.P$4, U$27.P$7, U$27.P$9, U$28.P$2, U$28.P$4, U$28.P$7, U$28.P$9, U$29.P$2, U$29.P$4, U$29.P$7, U$29.P$9, U$30.6
5V5: R11.1, U$31.P$2, U$31.P$4, U$31.P$7, U$31.P$9, U$32.P$2, U$32.P$4, U$32.P$7, U$32.P$9, U$33.P$2, U$33.P$4, U$33.P$7, U$33.P$9, U$34.P$2, U$34.P$4, U$34.P$7, U$34.P$9, U$35.P$2, U$35.P$4, U$35.P$7, U$35.P$9, U$36.6
5V6: R13.1, U$37.P$2, U$37.P$4, U$37.P$7, U$37.P$9, U$38.P$2, U$38.P$4, U$38.P$7, U$38.P$9, U$39.P$2, U$39.P$4, U$39.P$7, U$39.P$9, U$40.P$2, U$40.P$4, U$40.P$7, U$40.P$9, U$41.P$2, U$41.P$4, U$41.P$7, U$41.P$9, U$42.6
5V7: R15.1, U$43.P$2, U$43.P$4, U$43.P$7, U$43.P$9, U$44.P$2, U$44.P$4, U$44.P$7, U$44.P$9, U$45.P$2, U$45.P$4, U$45.P$7, U$45.P$9, U$46.P$2, U$46.P$4, U$46.P$7, U$46.P$9, U$47.P$2, U$47.P$4, U$47.P$7, U$47.P$9, U$48.6
DATA: R2.2, U$2.P$3, U$2.P$8, U$3.P$3, U$3.P$8, U$4.P$3, U$4.P$8, U$5.P$3, U$5.P$8, U$6.P$3, U$6.P$8
DATA1: R4.2, U$1.P$3, U$1.P$8, U$8.P$3, U$8.P$8, U$9.P$3, U$9.P$8, U$10.P$3, U$10.P$8, U$11.P$3, U$11.P$8
DATA2: R6.2, U$13.P$3, U$13.P$8, U$14.P$3, U$14.P$8, U$15.P$3, U$15.P$8, U$16.P$3, U$16.P$8, U$17.P$3, U$17.P$8
DATA3: R8.2, U$19.P$3, U$19.P$8, U$20.P$3, U$20.P$8, U$21.P$3, U$21.P$8, U$22.P$3, U$22.P$8, U$23.P$3, U$23.P$8
DATA4: R10.2, U$25.P$3, U$25.P$8, U$26.P$3, U$26.P$8, U$27.P$3, U$27.P$8, U$28.P$3, U$28.P$8, U$29.P$3, U$29.P$8
DATA5: R12.2, U$31.P$3, U$31.P$8, U$32.P$3, U$32.P$8, U$33.P$3, U$33.P$8, U$34.P$3, U$34.P$8, U$35.P$3, U$35.P$8
DATA6: R14.2, U$37.P$3, U$37.P$8, U$38.P$3, U$38.P$8, U$39.P$3, U$39.P$8, U$40.P$3, U$40.P$8, U$41.P$3, U$41.P$8
DATA7: R16.2, U$43.P$3, U$43.P$8, U$44.P$3, U$44.P$8, U$45.P$3, U$45.P$8, U$46.P$3, U$46.P$8, U$47.P$3, U$47.P$8
GND: C1.2, U$2.P$1, U$2.P$5, U$2.P$6, U$2.P$10, U$3.P$1, U$3.P$5, U$3.P$6, U$3.P$10, U$4.P$1, U$4.P$5, U$4.P$6, U$4.P$10, U$5.P$1, U$5.P$5, U$5.P$6, U$5.P$10, U$6.P$1, U$6.P$5, U$6.P$6, U$6.P$10, U$7.4
GND1: C2.2, U$1.P$1, U$1.P$5, U$1.P$6, U$1.P$10, U$8.P$1, U$8.P$5, U$8.P$6, U$8.P$10, U$9.P$1, U$9.P$5, U$9.P$6, U$9.P$10, U$10.P$1, U$10.P$5, U$10.P$6, U$10.P$10, U$11.P$1, U$11.P$5, U$11.P$6, U$11.P$10, U$12.4
GND2: C3.2, U$13.P$1, U$13.P$5, U$13.P$6, U$13.P$10, U$14.P$1, U$14.P$5, U$14.P$6, U$14.P$10, U$15.P$1, U$15.P$5, U$15.P$6, U$15.P$10, U$16.P$1, U$16.P$5, U$16.P$6, U$16.P$10, U$17.P$1, U$17.P$5, U$17.P$6, U$17.P$10, U$18.4
GND3: C4.2, U$19.P$1, U$19.P$5, U$19.P$6, U$19.P$10, U$20.P$1, U$20.P$5, U$20.P$6, U$20.P$10, U$21.P$1, U$21.P$5, U$21.P$6, U$21.P$10, U$22.P$1, U$22.P$5, U$22.P$6, U$22.P$10, U$23.P$1, U$23.P$5, U$23.P$6, U$23.P$10, U$24.4
GND4: C5.2, U$25.P$1, U$25.P$5, U$25.P$6, U$25.P$10, U$26.P$1, U$26.P$5, U$26.P$6, U$26.P$10, U$27.P$1, U$27.P$5, U$27.P$6, U$27.P$10, U$28.P$1, U$28.P$5, U$28.P$6, U$28.P$10, U$29.P$1, U$29.P$5, U$29.P$6, U$29.P$10, U$30.4
GND5: C6.2, U$31.P$1, U$31.P$5, U$31.P$6, U$31.P$10, U$32.P$1, U$32.P$5, U$32.P$6, U$32.P$10, U$33.P$1, U$33.P$5, U$33.P$6, U$33.P$10, U$34.P$1, U$34.P$5, U$34.P$6, U$34.P$10, U$35.P$1, U$35.P$5, U$35.P$6, U$35.P$10, U$36.4
GND6: C7.2, U$37.P$1, U$37.P$5, U$37.P$6, U$37.P$10, U$38.P$1, U$38.P$5, U$38.P$6, U$38.P$10, U$39.P$1, U$39.P$5, U$39.P$6, U$39.P$10, U$40.P$1, U$40.P$5, U$40.P$6, U$40.P$10, U$41.P$1, U$41.P$5, U$41.P$6, U$41.P$10, U$42.4
GND7: C8.2, U$43.P$1, U$43.P$5, U$43.P$6, U$43.P$10, U$44.P$1, U$44.P$5, U$44.P$6, U$44.P$10, U$45.P$1, U$45.P$5, U$45.P$6, U$45.P$10, U$46.P$1, U$46.P$5, U$46.P$6, U$46.P$10, U$47.P$1, U$47.P$5, U$47.P$6, U$47.P$10, U$48.4
unnamed: C1.1, R1.2, U$7.3
unnamed: R2.1, U$7.1
unnamed: C2.1, R3.2, U$12.3
unnamed: R4.1, U$12.1
unnamed: C3.1, R5.2, U$18.3
unnamed: R6.1, U$18.1
unnamed: C4.1, R7.2, U$24.3
unnamed: R8.1, U$24.1
unnamed: C5.1, R9.2, U$30.3
unnamed: R10.1, U$30.1
unnamed: C6.1, R11.2, U$36.3
unnamed: R12.1, U$36.1
unnamed: C7.1, R13.2, U$42.3
unnamed: R14.1, U$42.1
unnamed: C8.1, R15.2, U$48.3
unnamed: R16.1, U$48.1

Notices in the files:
parts and their libraries:
SparkFun-Aesthetics: Licensing: Creative Commons ShareAlike 4.0 International - https://creativecommons.org/licenses/by-sa/4.0
